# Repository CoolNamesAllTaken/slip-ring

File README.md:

# slip-ring
Open source 4 channel pancake slip ring for rotating hardware projects!

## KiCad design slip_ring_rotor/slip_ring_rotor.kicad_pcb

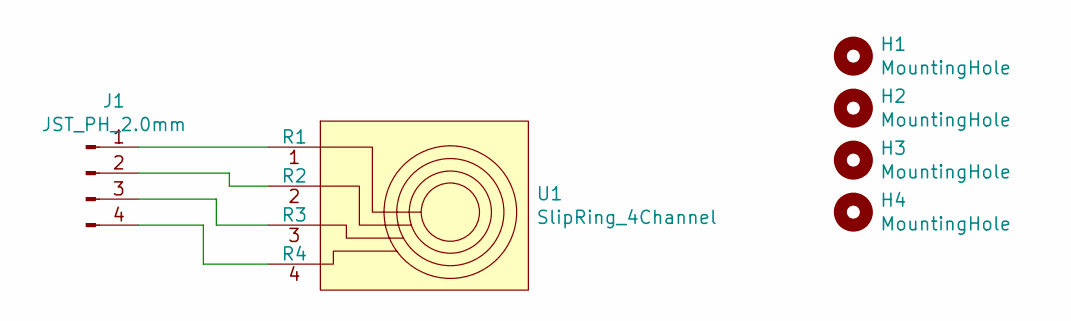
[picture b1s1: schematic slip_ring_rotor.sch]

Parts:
H1, H2, H3, H4: MountingHole; MountingHole_3.2mm_M3
J1: JST_PH_2.0mm; JST_PH_B4B-PH-K_1x04_P2.00mm_Vertical
U1: SlipRing_4Channel; SlipRingRotor_4Channel

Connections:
unnamed: J1.1, U1.1 (R1)
unnamed: J1.2, U1.2 (R2)
unnamed: J1.3, U1.3 (R3)
unnamed: J1.4, U1.4 (R4)

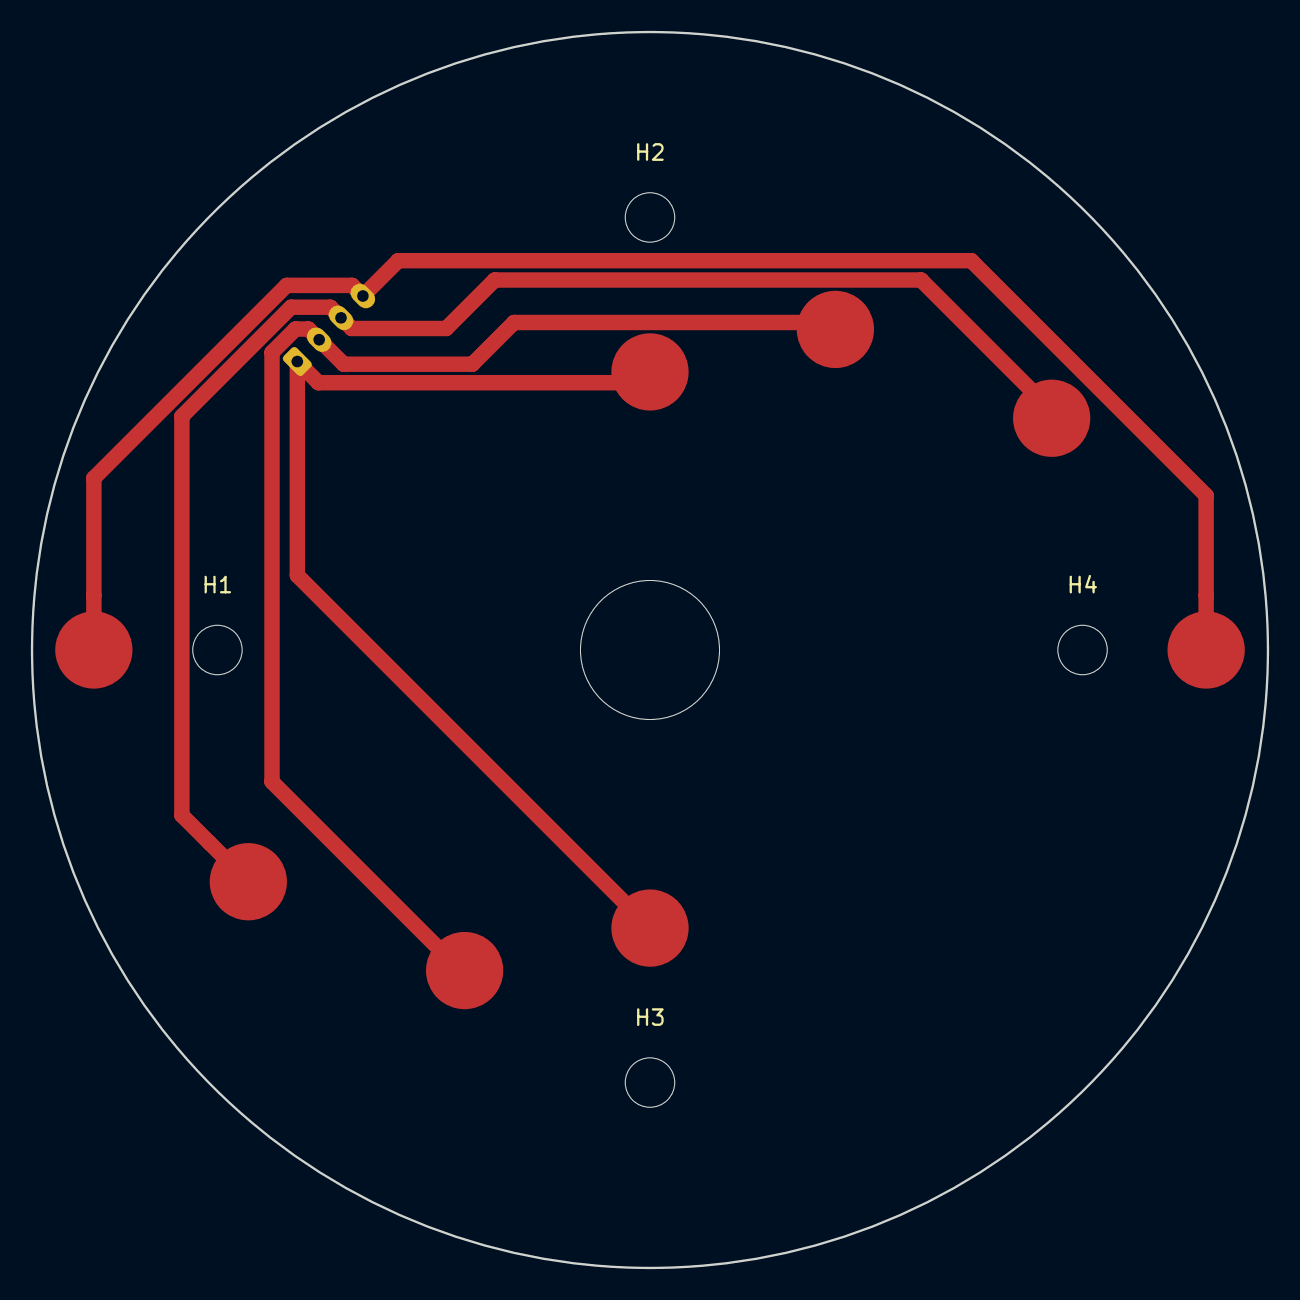
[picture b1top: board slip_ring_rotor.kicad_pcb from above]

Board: 2 copper layers, 80.0 x 80.0 mm, 6 parts (1 on the bottom side), 4 nets.

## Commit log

2020-08-02 Dump leftovers
